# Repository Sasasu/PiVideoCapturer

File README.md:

# PiVideoCapturer

A video capturer using TC358840XBG and arm SoC

Linux driver for [Linux 4.x](https://patchwork.kernel.org/project/linux-media/patch/44d2d84d-f18d-9c80-977f-8a2b8675e70a@xs4all.nl/) and [Linux 5.x](https://github.com/Sasasu/kernel/commit/2ac963e2eb28087317501f061d04d1e15ed70adb)

Also a [DTS example](https://github.com/Sasasu/kernel/commit/191d50bea6500b790de900fb8ab7bc9170189c27).

And a [debugging driver](https://github.com/Sasasu/kernel/blob/nanopi4-linux-v4.4.y/drivers/media/i2c/tc358840.c) for RK3399 with kernel 4.4.

License: GPLv3

----

TC358840XBG is completely EOL now. I personally recommend use RK3588 instead, RK3588 has a HDMI IN port.

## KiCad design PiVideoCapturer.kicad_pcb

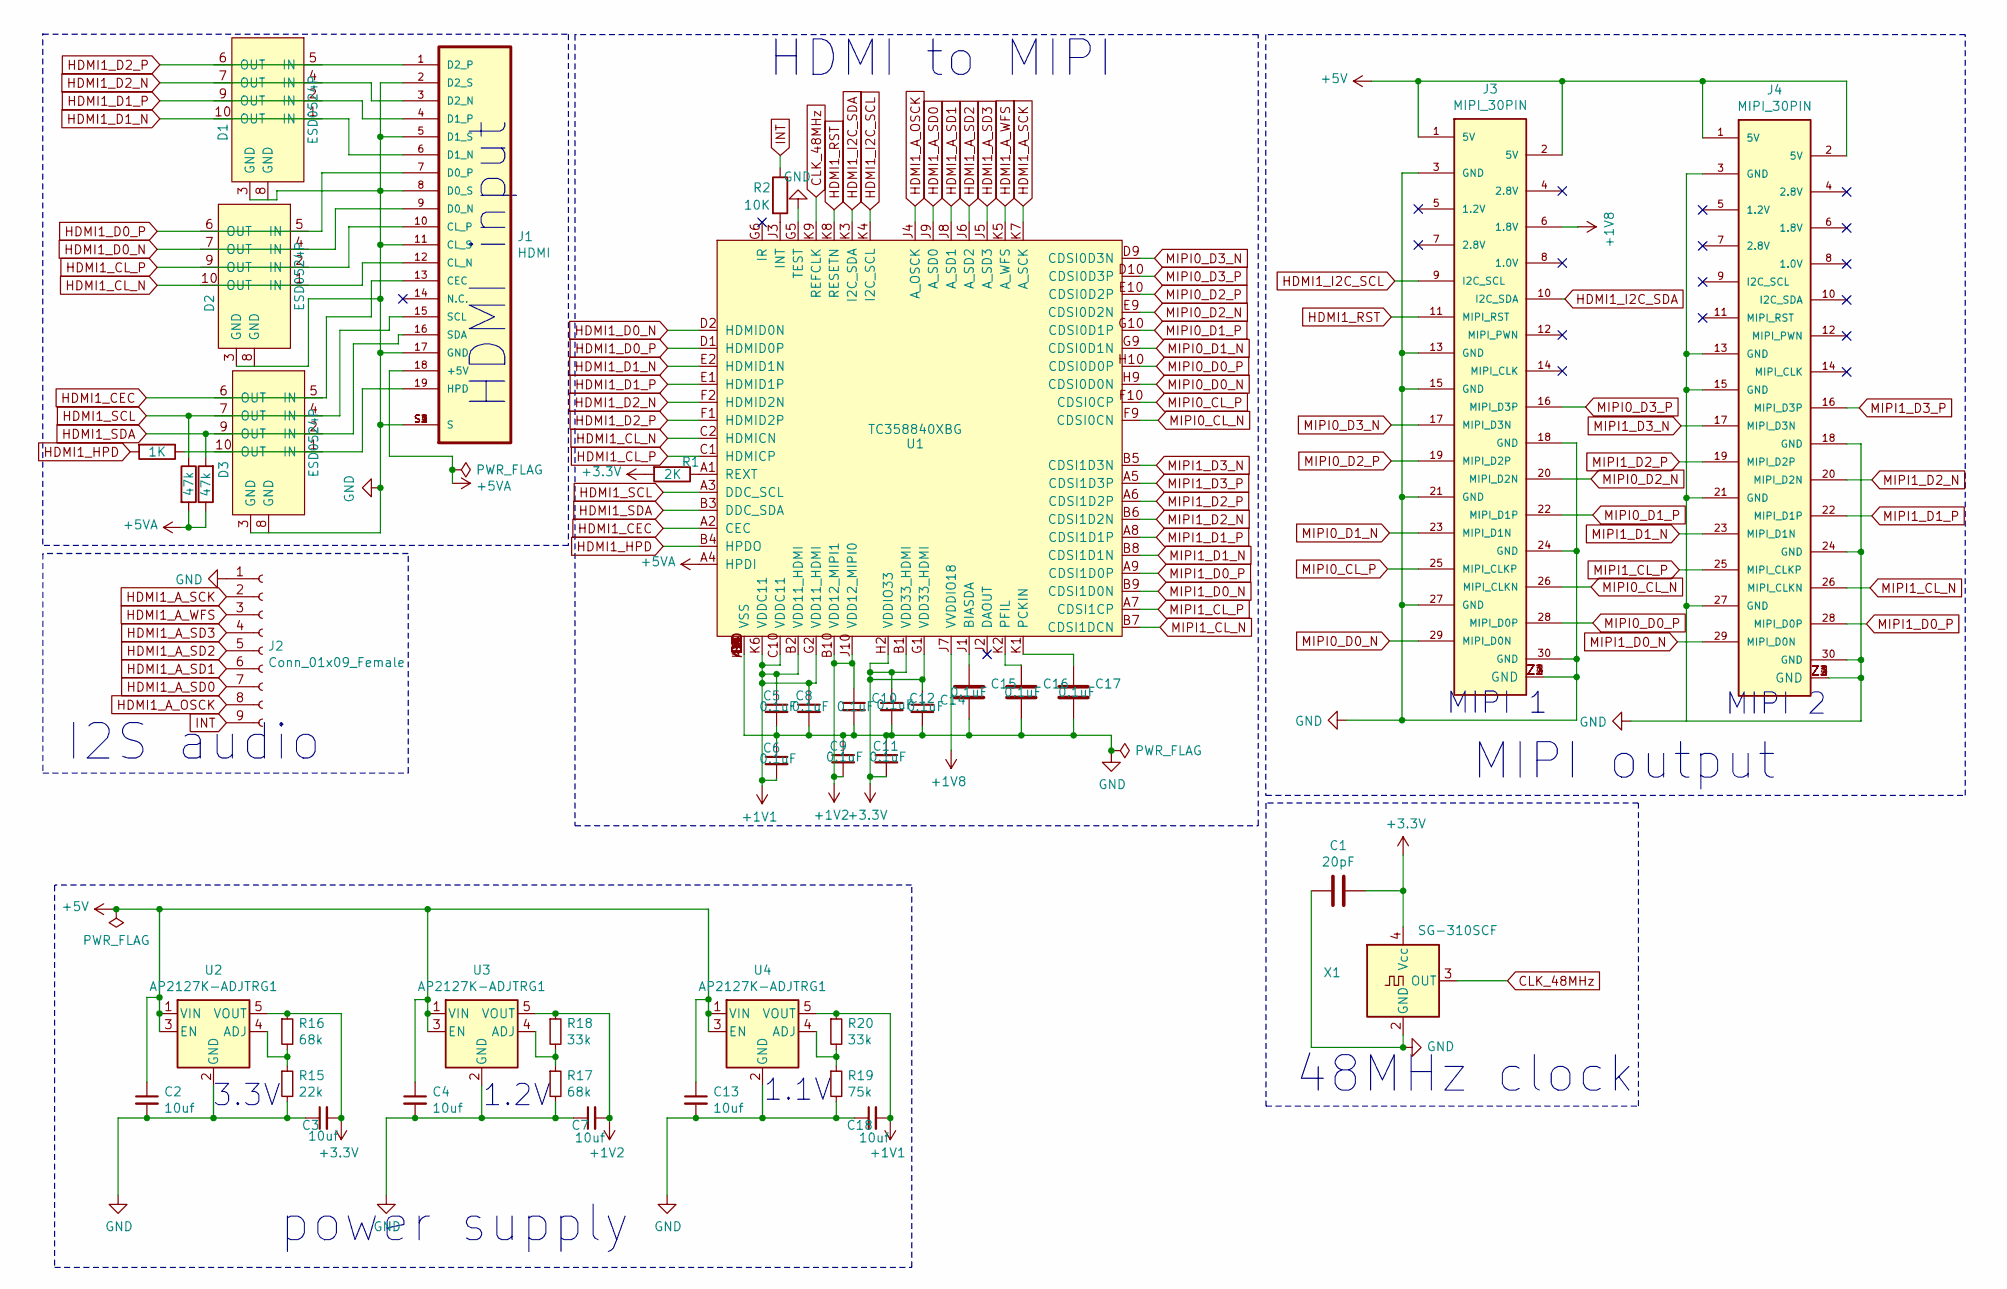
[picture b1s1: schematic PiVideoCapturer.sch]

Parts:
C1: 20pF; C_0402_1005Metric
C2, C3, C4, C7, C13, C18: 10uf; C_0402_1005Metric
C5, C6, C8, C9, C10, C11, C12, C14, C15, C16, C17: 0.1uF; C_0402_1005Metric
D1, D2, D3: ESD0524P; Diodes_UDFN-10_1.0x2.5mm_P0.5mm
J1: HDMI; TE_5-1903015-5
J2: Conn_01x09_Female; PinSocket_1x09_P2.54mm_Vertical
J3, J4: MIPI_30PIN; MIPI_30PIN_FPC_0.5mm
R1: 2K; R_0402_1005Metric
R2: 10K; R_0402_1005Metric
R10, R12: 47k; R_0402_1005Metric
R11: 1K; R_0402_1005Metric
R15: 22k; R_0402_1005Metric
R16, R17: 68k; R_0402_1005Metric
R18, R20: 33k; R_0402_1005Metric
R19: 75k; R_0402_1005Metric
U1: TC358840XBG; BGA80C65P10X10_700X700X100N
U2, U3, U4: AP2127K-ADJTRG1; SOT-23-5
X1: SG-310SCF; Crystal_SMD_3225-4Pin_3.2x2.5mm

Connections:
+1V1: C5.1, C6.2, C8.1, C18.2, R20.1, U1.B2 (VDD11_HDMI), U1.C10 (VDDC11), U1.G2 (VDD11_HDMI), U1.K6 (VDDC11), U4.5 (VOUT)
+1V2: C7.2, C9.2, C10.1, R18.1, U1.B10 (VDD12_MIPI1), U1.J10 (VDD12_MIPI0), U3.5 (VOUT)
+1V8: J3.6 (1.8V), U1.J7 (VVDDIO18)
+3V3: C1.1, C3.2, C11.2, C12.1, C14.1, R1.2, R16.1, U1.B1 (VDD33_HDMI), U1.G1 (VDD33_HDMI), U1.H2 (VDDIO33), U2.5 (VOUT), X1.4 (Vcc)
+5V: C2.1, C4.1, C13.1, J3.1 (5V), J3.2 (5V), J4.1 (5V), J4.2 (5V), U2.1 (VIN), U2.3 (EN), U3.1 (VIN), U3.3 (EN), U4.1 (VIN), U4.3 (EN)
+5VA: J1.18 (+5V), R10.2, R12.1, U1.A4 (HPDI)
CLK_48MHz: U1.K9 (REFCLK), X1.3 (OUT)
GND: C1.2, C2.2, C3.1, C4.2, C5.2, C6.1, C7.1, C8.2, C9.1, C10.2, C11.1, C12.2, C13.2, C14.2, C15.1, C16.1, C17.1, C18.1, D1.3 (GND), D2.3 (GND), D3.3 (GND), J1.2 (D2_S), J1.5 (D1_S), J1.8 (D0_S), J1.11 (CL_S), J1.17 (GND), J1.S1 (S), J1.S2 (S), J1.S3 (S), J1.S4 (S), J2.1, J3.3 (GND), J3.13 (GND), J3.15 (GND), J3.18 (GND), J3.21 (GND), J3.24 (GND), J3.27 (GND), J3.30 (GND), J3.Z1 (GND), J3.Z2 (GND), J3.Z3 (GND), J3.Z4 (GND), J4.3 (GND), J4.13 (GND), J4.15 (GND), J4.18 (GND), J4.21 (GND), J4.24 (GND), J4.27 (GND), J4.30 (GND), J4.Z1 (GND), J4.Z2 (GND), J4.Z3 (GND), J4.Z4 (GND), R15.2, R17.2, R19.2, U1.A10 (VSS), U1.C9 (VSS), U1.D4 (VSS), U1.D5 (VSS), U1.D6 (VSS), U1.D7 (VSS), U1.E4 (VSS), U1.E5 (VSS), U1.E6 (VSS), U1.E7 (VSS), U1.F4 (VSS), U1.F5 (VSS), U1.F6 (VSS), U1.F7 (VSS), U1.G4 (VSS), U1.G5 (TEST), U1.G7 (VSS), U1.H1 (VSS), U1.K10 (VSS), U2.2 (GND), U3.2 (GND), U4.2 (GND), X1.2 (GND)
HDMI1_A_OSCK: J2.8, U1.J4 (A_OSCK)
HDMI1_A_SCK: J2.2, U1.K7 (A_SCK)
HDMI1_A_SD0: J2.7, U1.J9 (A_SD0)
HDMI1_A_SD1: J2.6, U1.J8 (A_SD1)
HDMI1_A_SD2: J2.5, U1.J6 (A_SD2)
HDMI1_A_SD3: J2.4, U1.J5 (A_SD3)
HDMI1_A_WFS: J2.3, U1.K5 (A_WFS)
HDMI1_CEC: J1.13 (CEC), U1.A2 (CEC)
HDMI1_CL_N: J1.12 (CL_N), U1.C2 (HDMICN)
HDMI1_CL_P: J1.10 (CL_P), U1.C1 (HDMICP)
HDMI1_D0_N: J1.9 (D0_N), U1.D2 (HDMID0N)
HDMI1_D0_P: J1.7 (D0_P), U1.D1 (HDMID0P)
HDMI1_D1_N: J1.6 (D1_N), U1.E2 (HDMID1N)
HDMI1_D1_P: J1.4 (D1_P), U1.E1 (HDMID1P)
HDMI1_D2_N: J1.3 (D2_N), U1.F2 (HDMID2N)
HDMI1_D2_P: J1.1 (D2_P), U1.F1 (HDMID2P)
HDMI1_HPD: R11.2, U1.B4 (HPDO)
HDMI1_I2C_SCL: J3.9 (I2C_SCL), U1.K4 (I2C_SCL)
HDMI1_I2C_SDA: J3.10 (I2C_SDA), U1.K3 (I2C_SDA)
HDMI1_RST: J3.11 (MIPI_RST), U1.K8 (RESETN)
HDMI1_SCL: J1.15 (SCL), R10.1, U1.A3 (DDC_SCL)
HDMI1_SDA: J1.16 (SDA), R12.2, U1.B3 (DDC_SDA)
INT: J2.9, R2.1
MIPI0_CL_N: J3.26 (MIPI_CLKN), U1.F9 (CDSI0CN)
MIPI0_CL_P: J3.25 (MIPI_CLKP), U1.F10 (CDSI0CP)
MIPI0_D0_N: J3.29 (MIPI_D0N), U1.H9 (CDSI0D0N)
MIPI0_D0_P: J3.28 (MIPI_D0P), U1.H10 (CDSI0D0P)
MIPI0_D1_N: J3.23 (MIPI_D1N), U1.G9 (CDSI0D1N)
MIPI0_D1_P: J3.22 (MIPI_D1P), U1.G10 (CDSI0D1P)
MIPI0_D2_N: J3.20 (MIPI_D2N), U1.E9 (CDSI0D2N)
MIPI0_D2_P: J3.19 (MIPI_D2P), U1.E10 (CDSI0D2P)
MIPI0_D3_N: J3.17 (MIPI_D3N), U1.D9 (CDSI0D3N)
MIPI0_D3_P: J3.16 (MIPI_D3P), U1.D10 (CDSI0D3P)
MIPI1_CL_N: J4.26 (MIPI_CLKN), U1.B7 (CDSI1DCN)
MIPI1_CL_P: J4.25 (MIPI_CLKP), U1.A7 (CDSI1CP)
MIPI1_D0_N: J4.29 (MIPI_D0N), U1.B9 (CDSI1D0N)
MIPI1_D0_P: J4.28 (MIPI_D0P), U1.A9 (CDSI1D0P)
MIPI1_D1_N: J4.23 (MIPI_D1N), U1.B8 (CDSI1D1N)
MIPI1_D1_P: J4.22 (MIPI_D1P), U1.A8 (CDSI1D1P)
MIPI1_D2_N: J4.20 (MIPI_D2N), U1.B6 (CDSI1D2N)
MIPI1_D2_P: J4.19 (MIPI_D2P), U1.A6 (CDSI1D2P)
MIPI1_D3_N: J4.17 (MIPI_D3N), U1.B5 (CDSI1D3N)
MIPI1_D3_P: J4.16 (MIPI_D3P), U1.A5 (CDSI1D3P)
unnamed: C15.2, U1.J1 (BIASDA)
unnamed: C16.2, U1.K2 (PFIL)
unnamed: C17.2, U1.K1 (PCKIN)
unnamed: J1.19 (HPD), R11.1
unnamed: R1.1, U1.A1 (REXT)
unnamed: R2.2, U1.J3 (INT)
unnamed: R15.1, R16.2, U2.4 (ADJ)
unnamed: R17.1, R18.2, U3.4 (ADJ)
unnamed: R19.1, R20.2, U4.4 (ADJ)

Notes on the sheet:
HDMI input
48MHz clock
I2S audio
MIPI 2
MIPI output
HDMI to MIPI
power supply
3.3V
1.2V
1.1V
MIPI 1

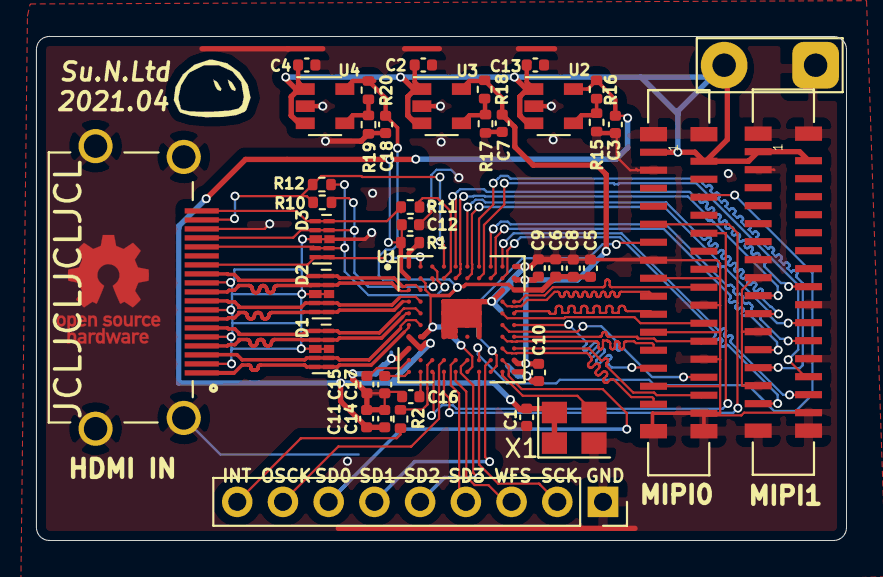
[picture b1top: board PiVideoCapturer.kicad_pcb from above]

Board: 2 copper layers, 45.0 x 28.0 mm, 41 parts (0 on the bottom side), 60 nets.

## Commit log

2021-02-12 Add README
2021-03-28 v0.9
2021-03-28 Add DTS example
2021-03-29 BOM: add FPC 30P 0.5mm vertical
2021-03-31 bom: add TC358840XBG part number
2021-04-05 Add debug driver
2021-04-05 new cover
2021-04-07 sync sch.pdf
2023-11-20 TC358840XBG EOL
